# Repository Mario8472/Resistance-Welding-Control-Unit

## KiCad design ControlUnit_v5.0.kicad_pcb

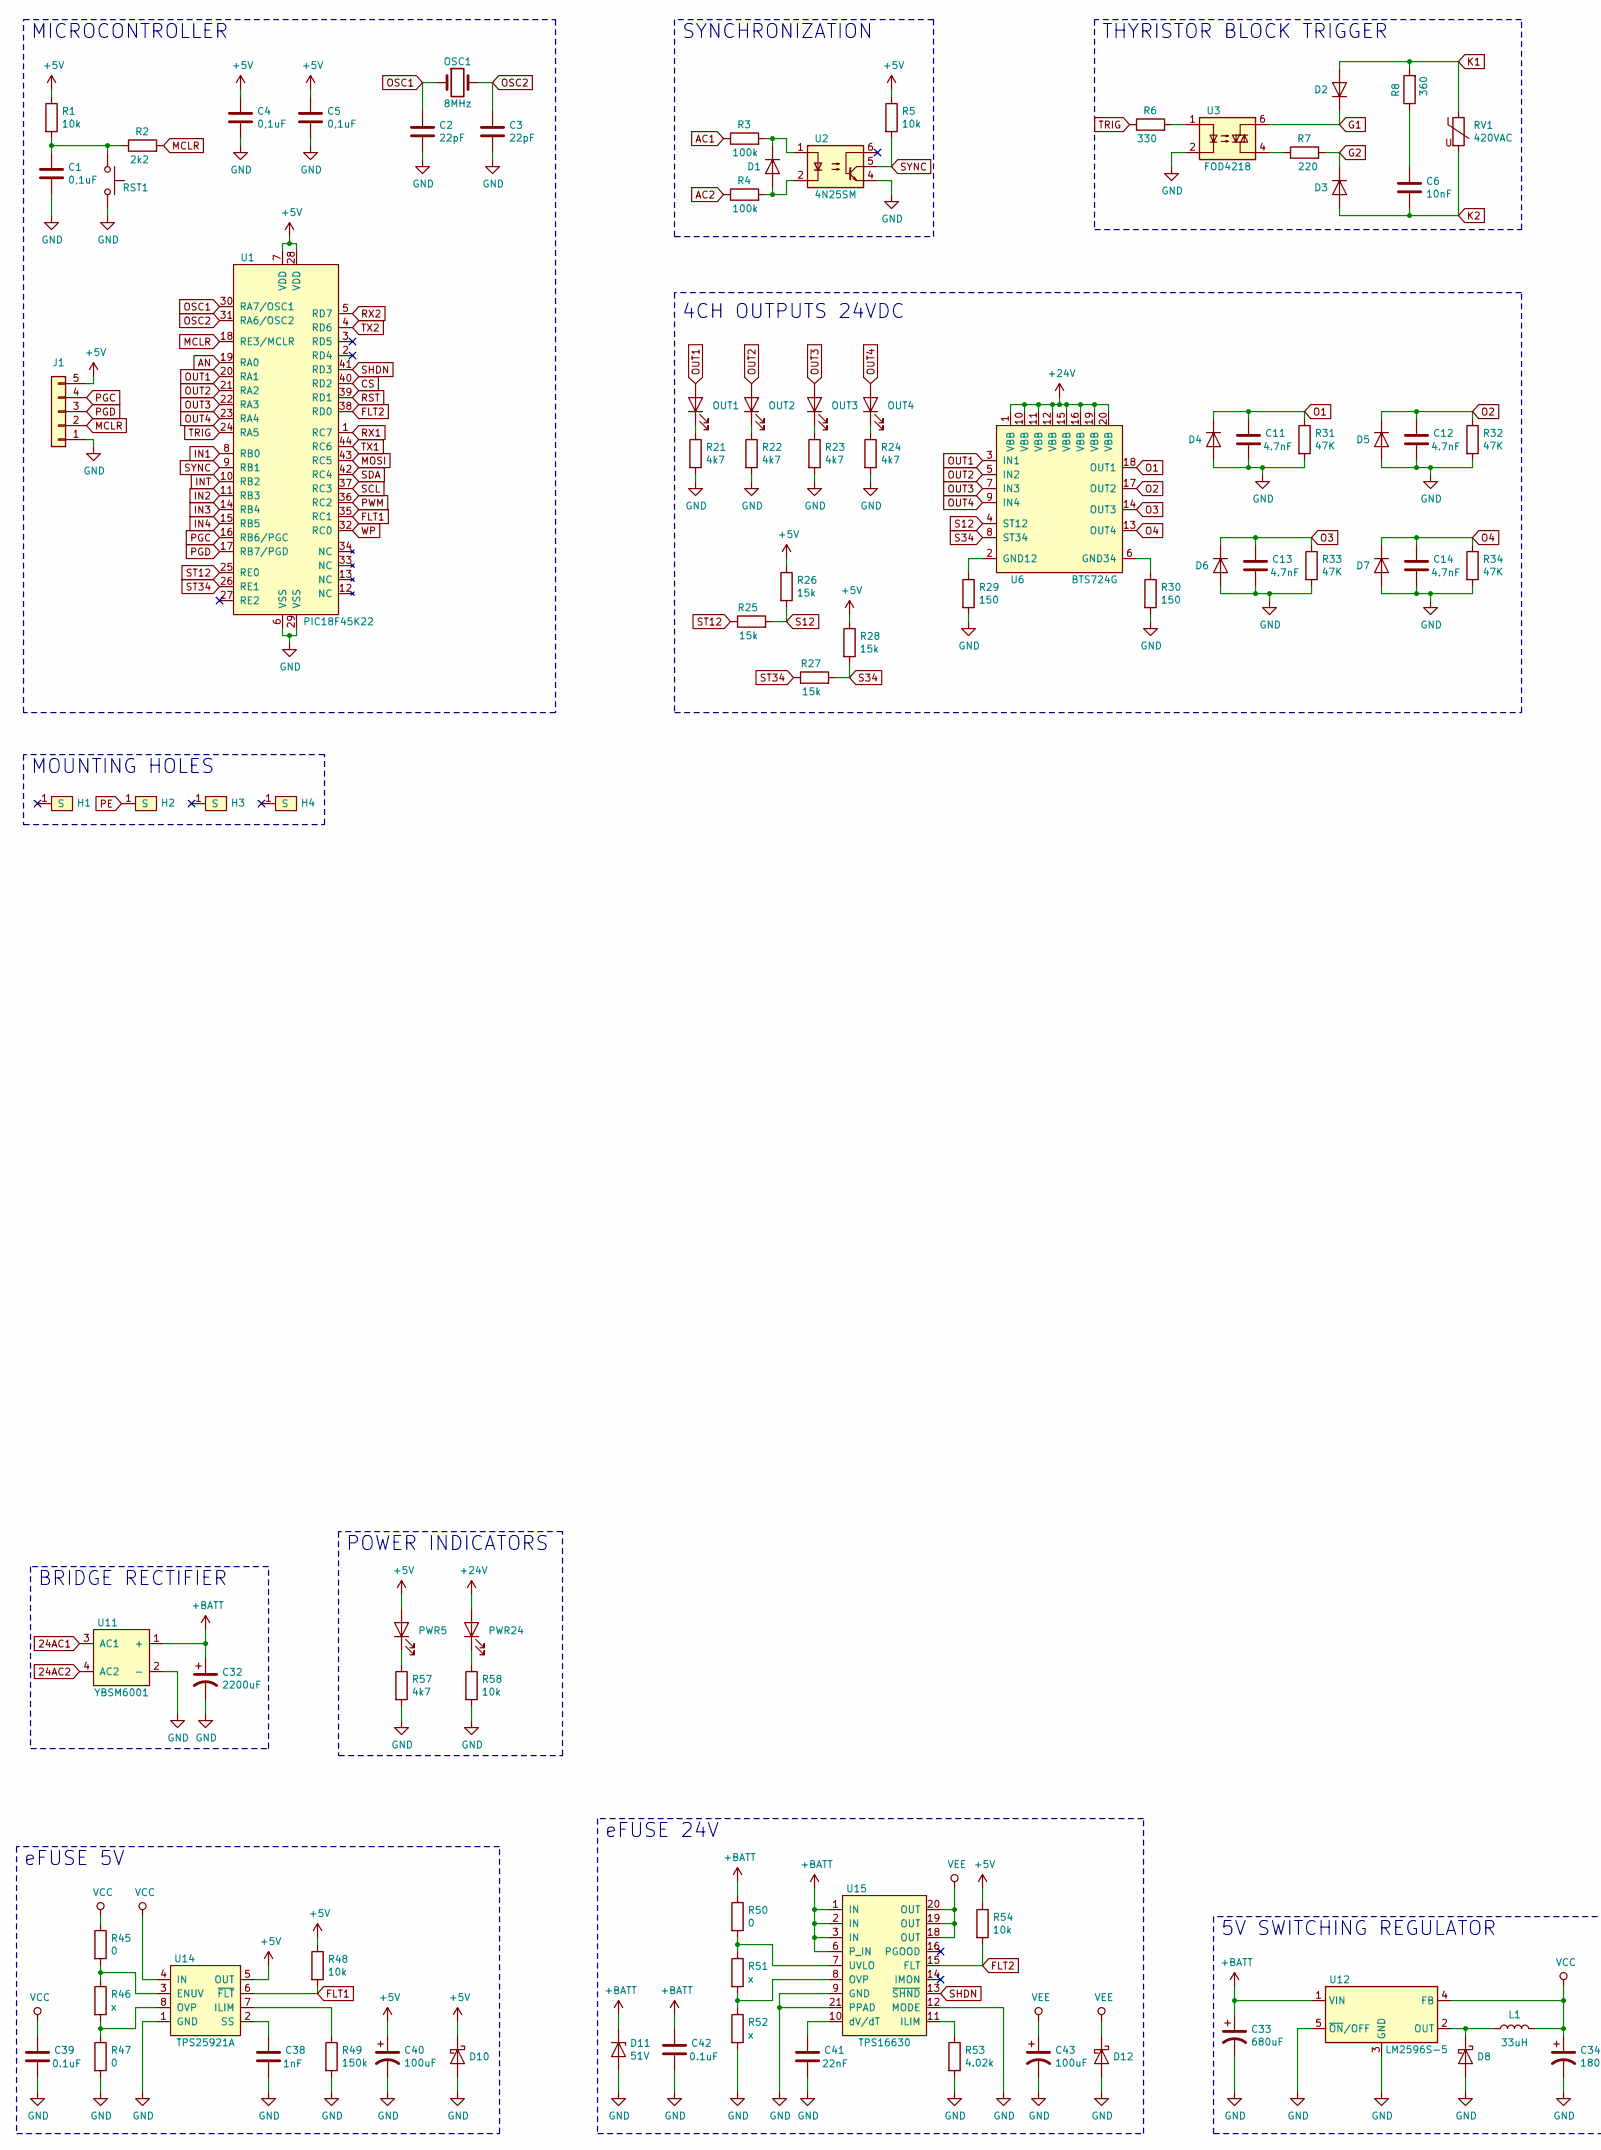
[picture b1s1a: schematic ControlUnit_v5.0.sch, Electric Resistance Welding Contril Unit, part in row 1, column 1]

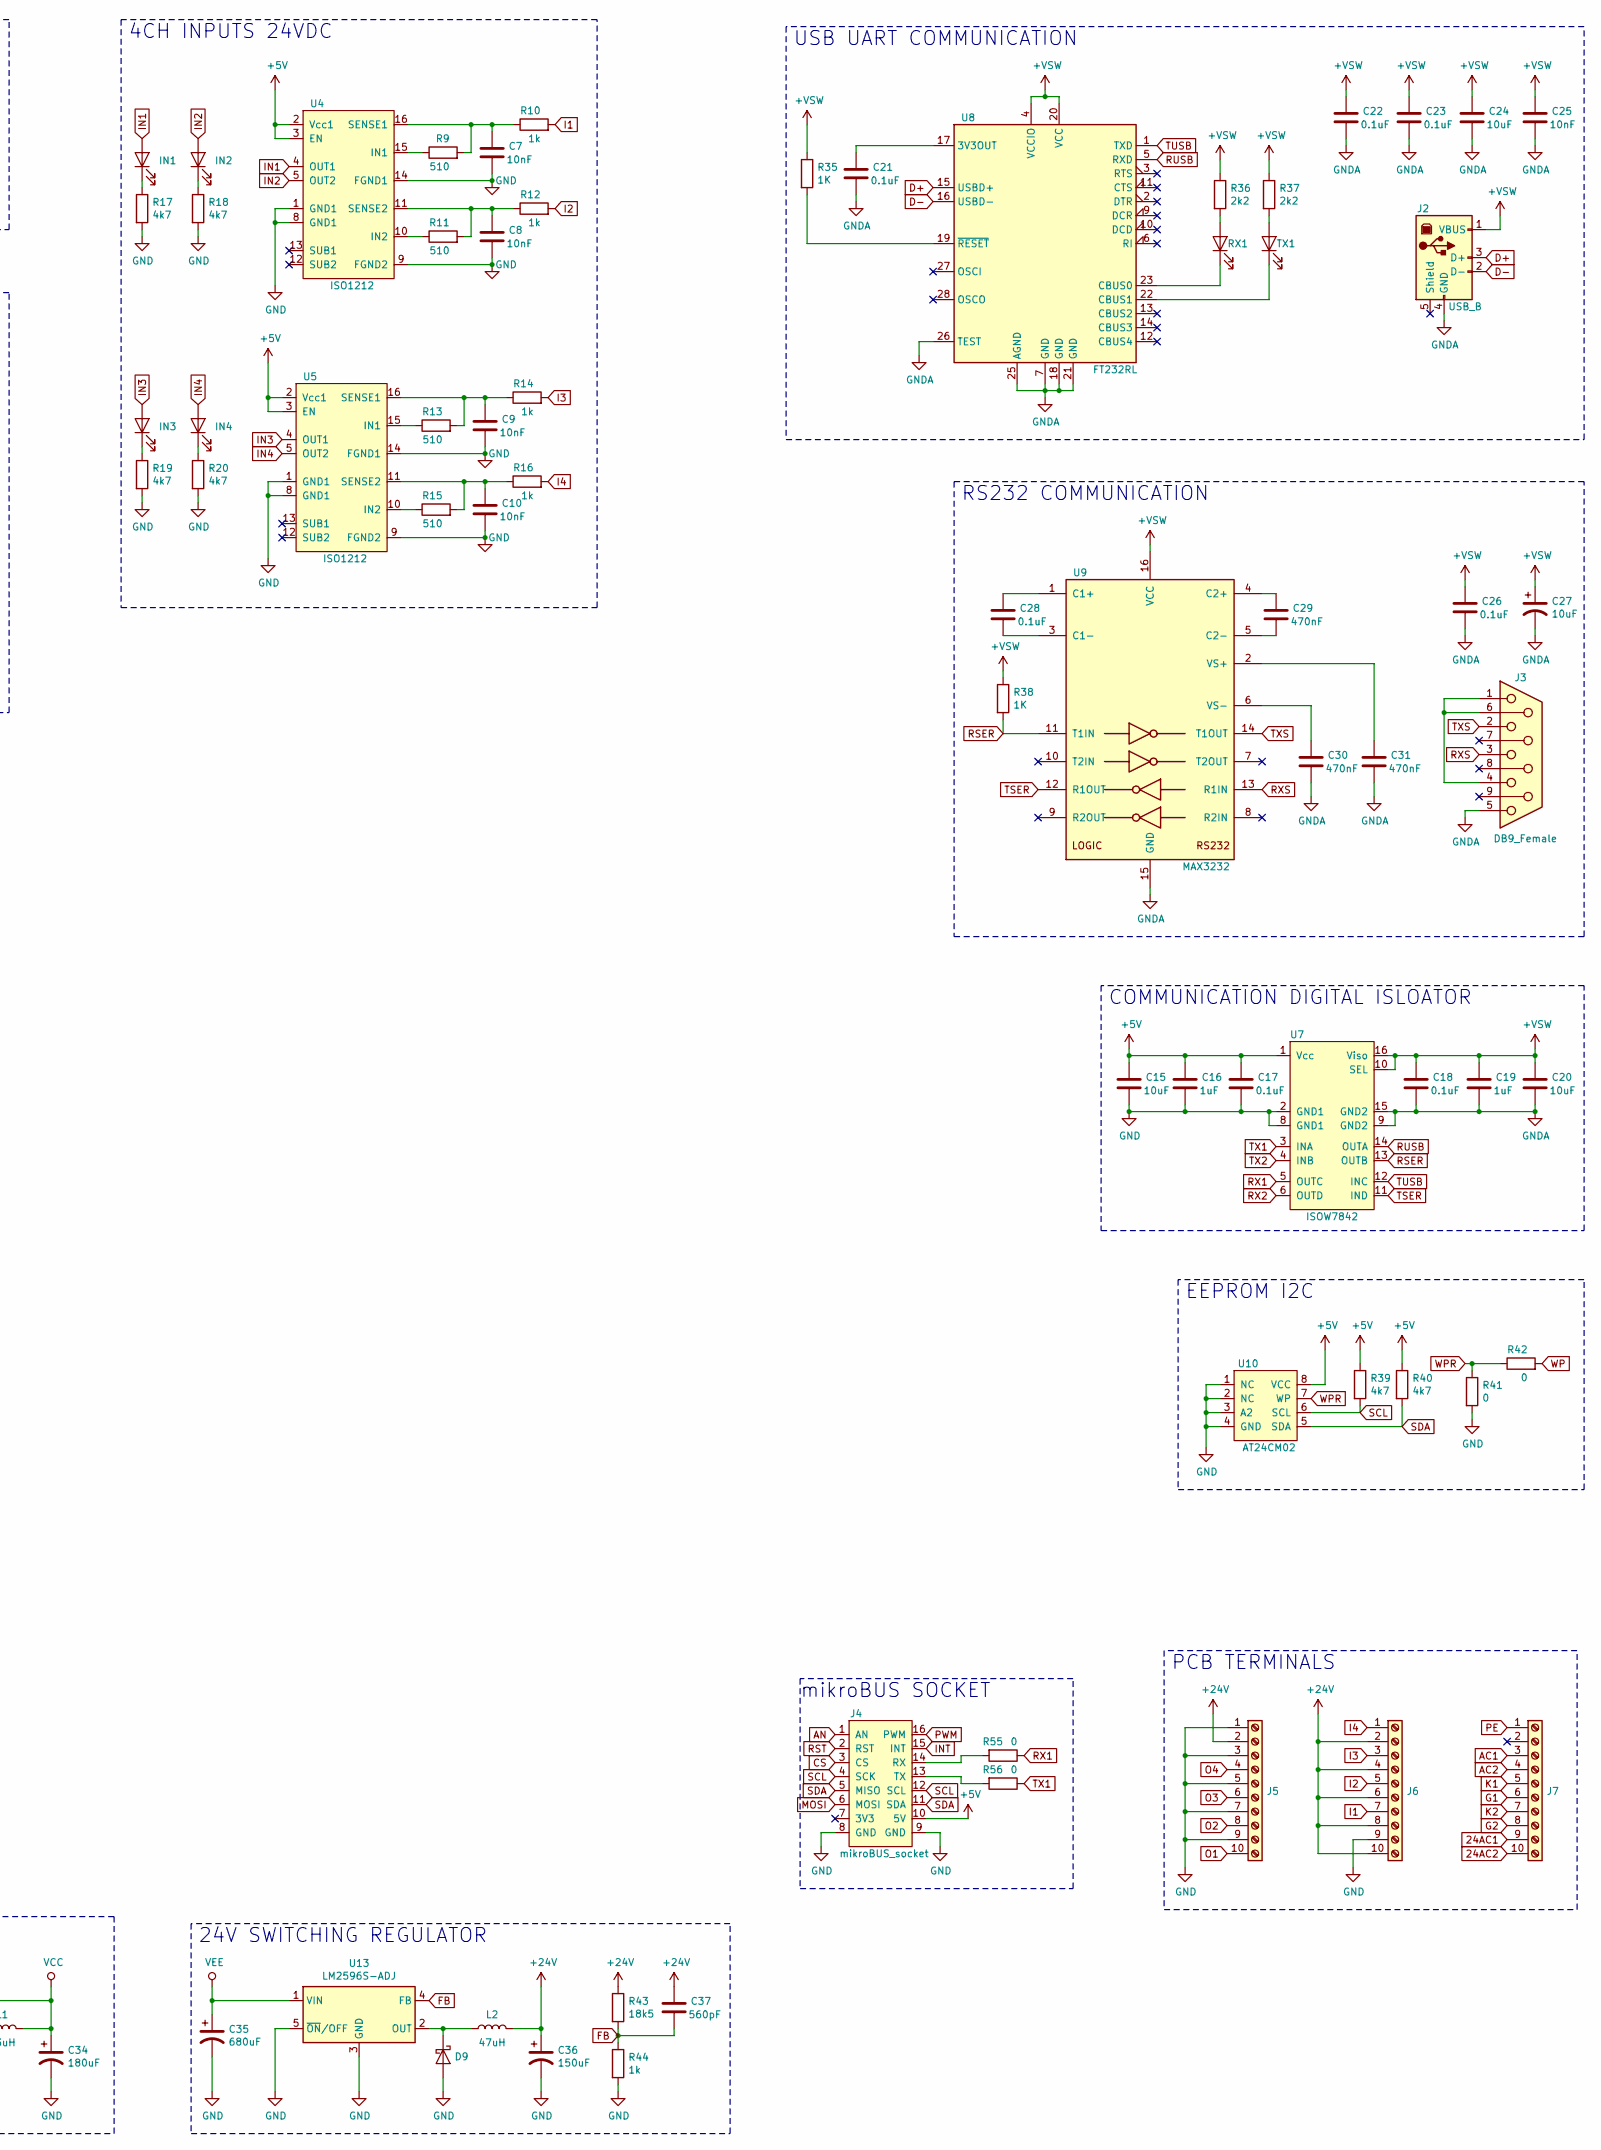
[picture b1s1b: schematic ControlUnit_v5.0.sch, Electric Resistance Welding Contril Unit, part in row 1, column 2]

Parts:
C1, C4, C5: 0,1uF; C_0805_2012Metric
C2, C3: 22pF; C_0805_2012Metric
C6: 10nF; Capacitor_R73QI21004030J
C7, C8, C9, C10, C25: 10nF; C_0805_2012Metric
C11, C12, C13, C14: 4.7nF; C_0805_2012Metric
C15, C20, C24: 10uF; C_0805_2012Metric
C16, C19: 1uF; C_0805_2012Metric
C17, C18, C21, C22, C23, C26, C28: 0.1uF; C_0805_2012Metric
C27: 10uF; CP_EIA-6032-20_AVX-F
C29, C30, C31: 470nF; C_0805_2012Metric
C32: 2200uF; CP_Radial_D16.0mm_P7.50mm
C33, C35: 680uF; CP_Radial_D12.5mm_P5.00mm
C34: 180uF; CP_Radial_D8.0mm_P3.50mm
C36: 150uF; CP_Radial_D10.0mm_P5.00mm
C37: 560pF; C_0805_2012Metric
C38: 1nF; C_0805_2012Metric
C39, C42: 0.1uF; C_1206_3216Metric
C40, C43: 100uF; CP_Radial_D10.0mm_P5.00mm
C41: 22nF; C_0805_2012Metric
D1, D2, D3: D; D_SMB
D4, D5, D6, D7: D; D_SMA
D8, D9: D_Schottky; D_DO-201AD_P12.70mm_Horizontal
D10: D_Schottky; D_SOD-123
D11: 51V; D_SMA
D12: D_Schottky; D_SMA
H1, H2, H3, H4: ScrewHoleM3
IN1, IN2, IN3, IN4: LED; LED_0805_2012Metric
J1: PROGRAM; PinHeader_1x05_P2.54mm_Vertical
J2: USB_B; USB-B_CONN
J3: DB9_Female; DSUB-9_CONN_F
J4: mikroBUS_socket
J5, J6, J7: Screw_Terminal_01x10; PCB_Screw_Terminal_5.08_10ways
L1: 33uH; HPI1206
L2: 47uH; HPI1206
OSC1: 8MHz; Crystal_SMD_HC49-SD
OUT1, OUT2, OUT3, OUT4: LED; LED_0805_2012Metric
PWR5, PWR24: LED; LED_0805_2012Metric
R1, R5, R48, R54: 10k; R_0805_2012Metric
R2, R36, R37: 2k2; R_0805_2012Metric
R3, R4: 100k; R_2512_6332Metric
R6: 330; R_0805_2012Metric
R7: 220; R_2512_6332Metric
R8: 360; R_2512_6332Metric
R9, R11, R13, R15: 510; R_1206_3216Metric
R10, R12, R14, R16: 1k; R_1206_3216Metric
R17, R18, R19, R20, R21, R22, R23, R24, R39, R40, R57: 4k7; R_0805_2012Metric
R25, R26, R27, R28: 15k; R_0805_2012Metric
R29, R30: 150; R_0805_2012Metric
R31, R32, R33, R34: 47K; R_0805_2012Metric
R35, R38: 1K; R_0805_2012Metric
R41, R42, R45, R47, R50, R55, R56: 0; R_0805_2012Metric
R43: 18k5; R_0805_2012Metric
R44: 1k; R_0805_2012Metric
R46, R51, R52: x; R_0805_2012Metric
R49: 150k; R_0805_2012Metric
R53: 4.02k; R_0805_2012Metric
R58: 10k; R_1206_3216Metric
RST1: SW_Push; TACTSWITCH6x6
RV1: 420VAC; VARISTOR_SIOV-S07K420
RX1: LED; LED_0805_2012Metric
TX1: LED; LED_0805_2012Metric
U1: PIC18F45K22; TQFP-44_10x10mm_P0.8mm
U2: 4N25SM; SMDIP-6_W9.53mm
U3: FOD4218; SMDIP-6_W9.53mm
U4, U5: ISO1212
U6: BTS724G; SOIC-20W_7.5x12.8mm_P1.27mm
U7: ISOW7842; SOIC-16W_7.5x10.3mm_P1.27mm
U8: FT232RL; SSOP-28_5.3x10.2mm_P0.65mm
U9: MAX3232; SOIC-16_3.9x9.9mm_P1.27mm
U10: AT24CM02; SOIC-8_3.9x4.9mm_P1.27mm
U11: YBSM6001; YBSM3001
U12: LM2596S-5; TO-263-5_TabPin3
U13: LM2596S-ADJ; TO-263-5_TabPin3
U14: TPS25921A; SOIC-8_3.9x4.9mm_P1.27mm
U15: TPS16630; ETSSOP-20-1EP_4.4x6.5mm_P0.65mm_EP3x4.2mm

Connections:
24AC1: J7.9, U11.3 (AC1)
24AC2: J7.10, U11.4 (AC2)
+5V: C4.1, C5.1, C15.1, C16.1, C17.1, C40.1, D10.1 (K), J1.5, J4.10 (5V), PWR5.2 (A), R1.1, R5.1, R26.1, R28.1, R39.1, R40.1, R48.1, R54.1, U1.7 (VDD), U1.28 (VDD), U4.2 (Vcc1), U4.3 (EN), U5.2 (Vcc1), U5.3 (EN), U7.1 (Vcc), U10.8 (VCC), U14.5 (OUT)
+24V: C36.1, C37.1, J5.2, J6.2, J6.4, J6.6, J6.8, J6.10, L2.2, PWR24.2 (A), R43.1, U6.1 (VBB), U6.10 (VBB), U6.11 (VBB), U6.12 (VBB), U6.15 (VBB), U6.16 (VBB), U6.19 (VBB), U6.20 (VBB)
+BATT: C32.1, C33.1, C42.1, D11.1 (K), R50.1, U11.1 (+), U12.1 (VIN), U15.1 (IN), U15.2 (IN), U15.3 (IN), U15.6 (P_IN)
+VSW: C18.1, C19.1, C20.1, C22.1, C23.1, C24.1, C25.1, C26.1, C27.1, J2.1 (VBUS), R35.1, R36.1, R37.1, R38.1, U7.10 (SEL), U7.16 (Viso), U8.4 (VCCIO), U8.20 (VCC), U9.16 (VCC)
AC1: J7.3, R3.1
AC2: J7.4, R4.1
AN: J4.1 (AN), U1.19 (RA0)
CS: J4.3 (CS), U1.40 (RD2)
D+: J2.3 (D+), U8.15 (USBD+)
D-: J2.2 (D-), U8.16 (USBD-)
FB: C37.2, R43.2, R44.1, U13.4 (FB)
FLT1: R48.2, U1.35 (RC1), U14.6 (~FLT)
FLT2: R54.2, U1.38 (RD0), U15.15 (FLT)
G1: D2.1 (K), J7.6, U3.6
G2: D3.1 (K), J7.8, R7.2
GND: C1.2, C2.2, C3.2, C4.2, C5.2, C7.2, C8.2, C9.2, C10.2, C11.2, C12.2, C13.2, C14.2, C15.2, C16.2, C17.2, C32.2, C33.2, C34.2, C35.2, C36.2, C38.2, C39.2, C40.2, C41.2, C42.2, C43.2, D4.2 (A), D5.2 (A), D6.2 (A), D7.2 (A), D8.2 (A), D9.2 (A), D10.2 (A), D11.2 (A), D12.2 (A), J1.1, J4.8 (GND), J4.9 (GND), J5.1, J5.3, J5.5, J5.7, J5.9, J6.9, R17.2, R18.2, R19.2, R20.2, R21.2, R22.2, R23.2, R24.2, R29.2, R30.2, R31.2, R32.2, R33.2, R34.2, R41.2, R44.2, R47.2, R49.2, R52.2, R53.2, R57.2, R58.2, RST1.2, U1.6 (VSS), U1.29 (VSS), U2.4, U3.2, U4.1 (GND1), U4.8 (GND1), U4.9 (FGND2), U4.14 (FGND1), U5.1 (GND1), U5.8 (GND1), U5.9 (FGND2), U5.14 (FGND1), U7.2 (GND1), U7.8 (GND1), U10.1 (NC), U10.2 (NC), U10.3 (A2), U10.4 (GND), U11.2 (-), U12.3 (GND), U12.5 (~ON~/OFF), U13.3 (GND), U13.5 (~ON~/OFF), U14.1 (GND), U15.9 (GND), U15.12 (MODE), U15.21 (PPAD)
GNDA: C18.2, C19.2, C20.2, C21.2, C22.2, C23.2, C24.2, C25.2, C26.2, C27.2, C30.2, C31.2, J2.4 (GND), J3.5, U7.9 (GND2), U7.15 (GND2), U8.7 (GND), U8.18 (GND), U8.21 (GND), U8.25 (AGND), U8.26 (TEST), U9.15 (GND)
I1: J6.7, R10.2
I2: J6.5, R12.2
I3: J6.3, R14.2
I4: J6.1, R16.2
IN1: IN1.2 (A), U1.8 (RB0), U4.4 (OUT1)
IN2: IN2.2 (A), U1.11 (RB3), U4.5 (OUT2)
IN3: IN3.2 (A), U1.14 (RB4), U5.4 (OUT1)
IN4: IN4.2 (A), U1.15 (RB5), U5.5 (OUT2)
INT: J4.15 (INT), U1.10 (RB2)
K1: D2.2 (A), J7.5, R8.2, RV1.1
K2: C6.2, D3.2 (A), J7.7, RV1.2
MCLR: J1.2, R2.2, U1.18 (RE3/MCLR)
MOSI: J4.6 (MOSI), U1.43 (RC5)
unnamed: C1.1, R1.2, R2.1, RST1.1
unnamed: C6.1, R8.1
unnamed: C7.1, R9.2, R10.1, U4.16 (SENSE1)
unnamed: C8.1, R11.2, R12.1, U4.11 (SENSE2)
unnamed: C9.1, R13.2, R14.1, U5.16 (SENSE1)
unnamed: C10.1, R15.2, R16.1, U5.11 (SENSE2)
unnamed: C21.1, U8.17 (3V3OUT)
unnamed: C28.1, U9.1 (C1+)
unnamed: C28.2, U9.3 (C1-)
unnamed: C29.1, U9.4 (C2+)
unnamed: C29.2, U9.5 (C2-)
unnamed: C30.1, U9.6 (VS-)
unnamed: C31.1, U9.2 (VS+)
unnamed: C38.1, U14.2 (SS)
unnamed: C41.1, U15.10 (dV/dT)
unnamed: D1.1 (K), R3.2, U2.1
unnamed: D1.2 (A), R4.2, U2.2
unnamed: D8.1 (K), L1.1, U12.2 (OUT)
unnamed: D9.1 (K), L2.1, U13.2 (OUT)
unnamed: IN1.1 (K), R17.1
unnamed: IN2.1 (K), R18.1
unnamed: IN3.1 (K), R19.1
unnamed: IN4.1 (K), R20.1
unnamed: J3.1, J3.4, J3.6
unnamed: J4.13 (TX), R56.2
unnamed: J4.14 (RX), R55.2
unnamed: OUT1.1 (K), R21.1
unnamed: OUT2.1 (K), R22.1
unnamed: OUT3.1 (K), R23.1
unnamed: OUT4.1 (K), R24.1
unnamed: PWR5.1 (K), R57.1
unnamed: PWR24.1 (K), R58.1
unnamed: R6.2, U3.1
unnamed: R7.1, U3.4
unnamed: R9.1, U4.15 (IN1)
unnamed: R11.1, U4.10 (IN2)
unnamed: R13.1, U5.15 (IN1)
unnamed: R15.1, U5.10 (IN2)
unnamed: R29.1, U6.2 (GND12)
unnamed: R30.1, U6.6 (GND34)
unnamed: R35.2, U8.19 (~RESET~)
unnamed: R36.2, RX1.2 (A)
unnamed: R37.2, TX1.2 (A)
unnamed: R45.2, R46.1, U14.3 (ENUV)
unnamed: R46.2, R47.1, U14.8 (OVP)
unnamed: R49.1, U14.7 (ILIM)
unnamed: R50.2, R51.1, U15.7 (UVLO)
unnamed: R51.2, R52.1, U15.8 (OVP)
unnamed: R53.1, U15.11 (ILIM)
unnamed: RX1.1 (K), U8.23 (CBUS0)
unnamed: TX1.1 (K), U8.22 (CBUS1)
O1: C11.1, D4.1 (K), J5.10, R31.1, U6.18 (OUT1)
O2: C12.1, D5.1 (K), J5.8, R32.1, U6.17 (OUT2)
O3: C13.1, D6.1 (K), J5.6, R33.1, U6.14 (OUT3)
O4: C14.1, D7.1 (K), J5.4, R34.1, U6.13 (OUT4)
OSC1: C2.1, OSC1.1, U1.30 (RA7/OSC1)
OSC2: C3.1, OSC1.2, U1.31 (RA6/OSC2)
OUT1: OUT1.2 (A), U1.20 (RA1), U6.3 (IN1)
OUT2: OUT2.2 (A), U1.21 (RA2), U6.5 (IN2)
OUT3: OUT3.2 (A), U1.22 (RA3), U6.7 (IN3)
OUT4: OUT4.2 (A), U1.23 (RA4), U6.9 (IN4)
PE: H2.1, J7.1
PGC: J1.4, U1.16 (RB6/PGC)
PGD: J1.3, U1.17 (RB7/PGD)
PWM: J4.16 (PWM), U1.36 (RC2)
RSER: R38.2, U7.13 (OUTB), U9.11 (T1IN)
RST: J4.2 (RST), U1.39 (RD1)
RUSB: U7.14 (OUTA), U8.5 (RXD)
RX1: R55.1, U1.1 (RC7), U7.5 (OUTC)
RX2: U1.5 (RD7), U7.6 (OUTD)
RXS: J3.3, U9.13 (R1IN)
S12: R25.2, R26.2, U6.4 (ST12)
S34: R27.2, R28.2, U6.8 (ST34)
SCL: J4.4 (SCK), J4.12 (SCL), R39.2, U1.37 (RC3), U10.6 (SCL)
SDA: J4.5 (MISO), J4.11 (SDA), R40.2, U1.42 (RC4), U10.5 (SDA)
SHDN: U1.41 (RD3), U15.13 (~SHND)
ST12: R25.1, U1.25 (RE0)
ST34: R27.1, U1.26 (RE1)
SYNC: R5.2, U1.9 (RB1), U2.5
TRIG: R6.1, U1.24 (RA5)
TSER: U7.11 (IND), U9.12 (R1OUT)
TUSB: U7.12 (INC), U8.1 (TXD)
TX1: R56.1, U1.44 (RC6), U7.3 (INA)
TX2: U1.4 (RD6), U7.4 (INB)
TXS: J3.2, U9.14 (T1OUT)
VCC: C34.1, C39.1, L1.2, R45.1, U12.4 (FB), U14.4 (IN)
VEE: C35.1, C43.1, D12.1 (K), U13.1 (VIN), U15.18 (OUT), U15.19 (OUT), U15.20 (OUT)
WP: R42.2, U1.32 (RC0)
WPR: R41.1, R42.1, U10.7 (WP)

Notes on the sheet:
MICROCONTROLLER
SYNCHRONIZATION
THYRISTOR BLOCK TRIGGER
4CH INPUTS 24VDC
4CH OUTPUTS 24VDC
COMMUNICATION DIGITAL ISLOATOR
USB UART COMMUNICATION
RS232 COMMUNICATION
EEPROM I2C
BRIDGE RECTIFIER
5V SWITCHING REGULATOR
24V SWITCHING REGULATOR
eFUSE 5V
eFUSE 24V
mikroBUS SOCKET
PCB TERMINALS
POWER INDICATORS
MOUNTING HOLES

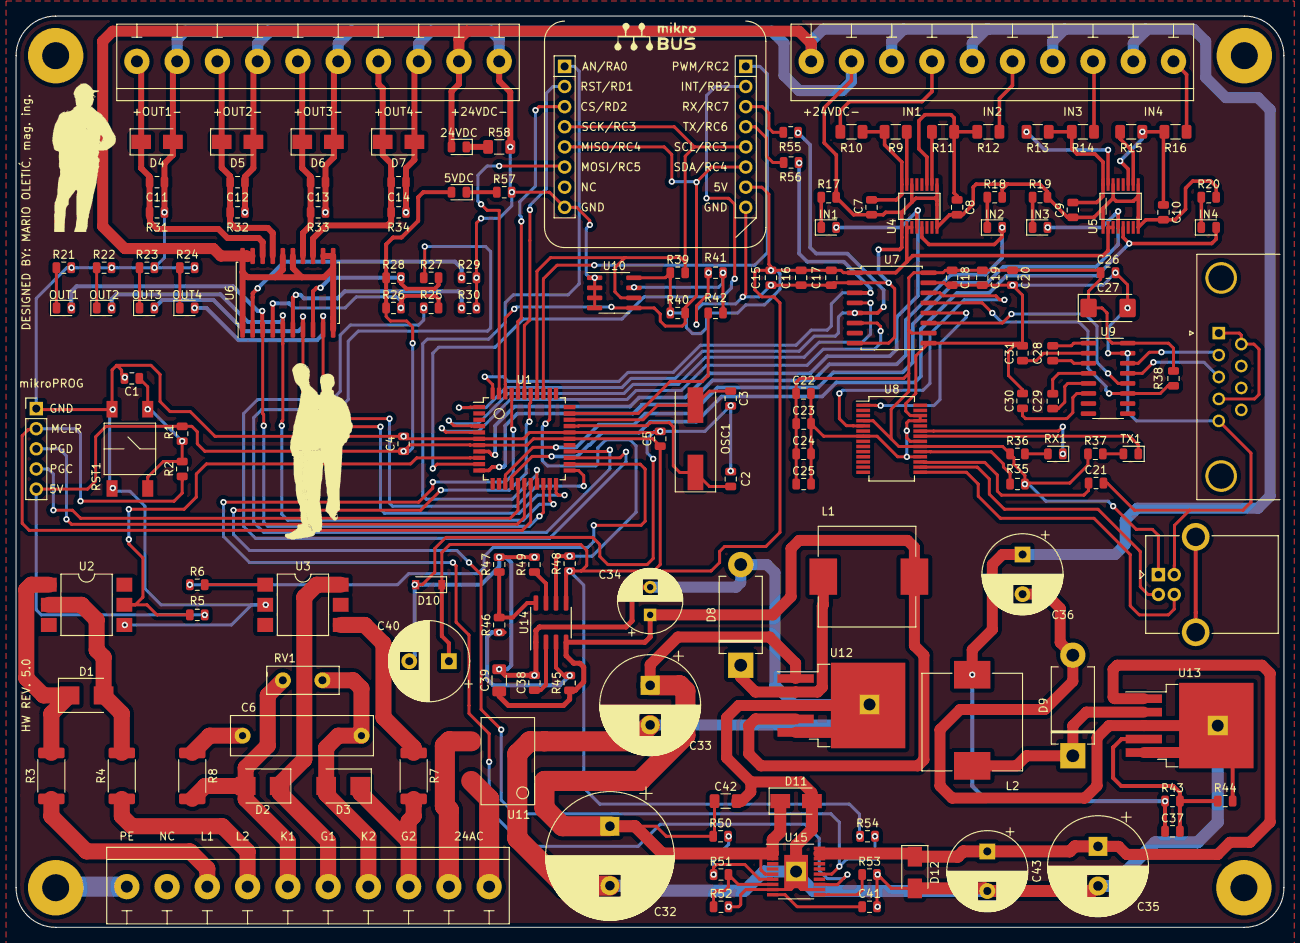
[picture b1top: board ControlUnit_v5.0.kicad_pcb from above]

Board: 2 copper layers, 160.0 x 115.0 mm, 156 parts (0 on the bottom side), 121 nets.
